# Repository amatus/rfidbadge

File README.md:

# RFID badge for DEF CON

## Controls

Press MENU to enter the menu system and to advance the selection.
Press SELECT to activate the selection.

Hold MENU to adjust the LCD contrast down (if the screen is all black).
Hold SELECT to adjust the LCD contrast up (if the screen is too light).

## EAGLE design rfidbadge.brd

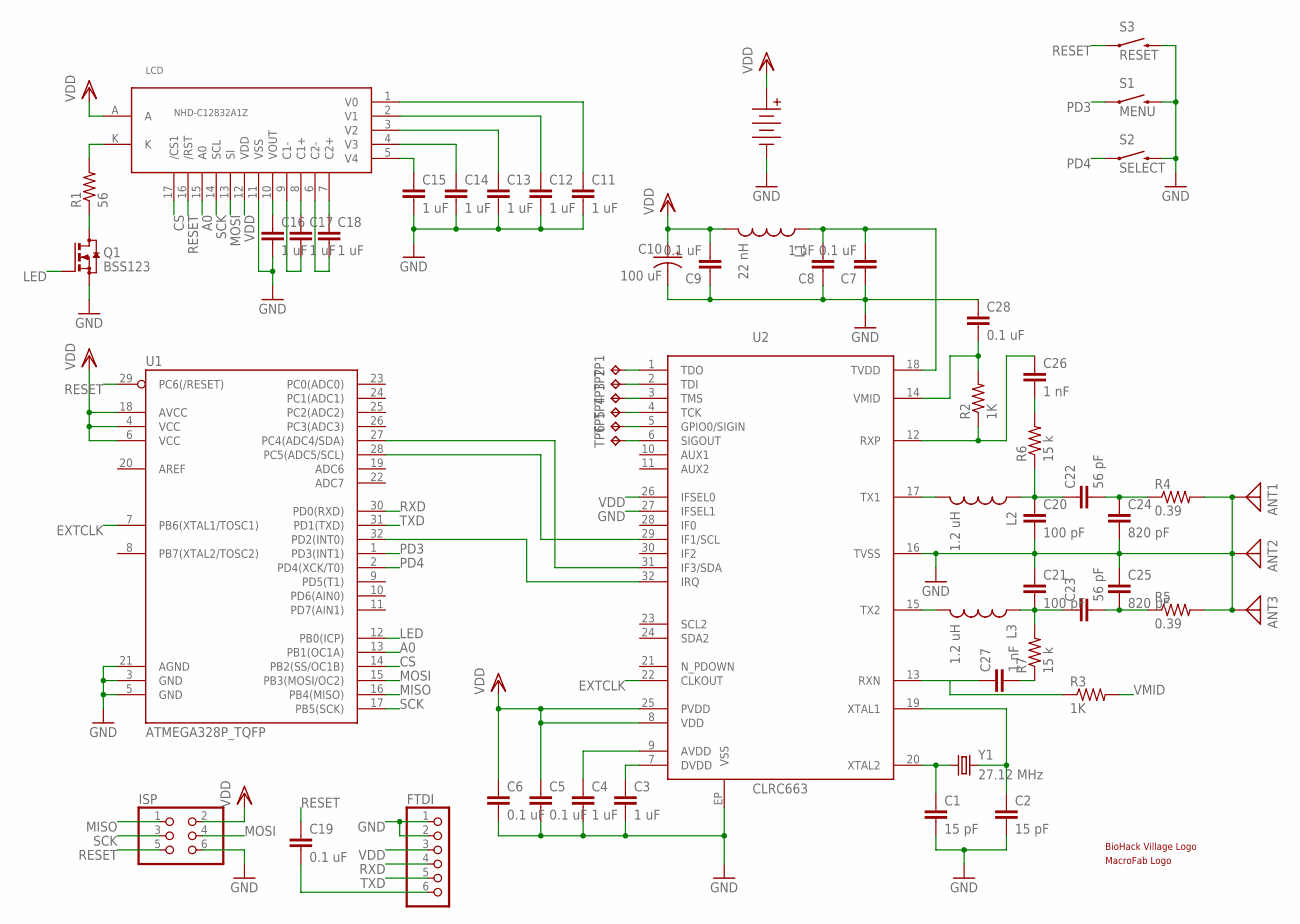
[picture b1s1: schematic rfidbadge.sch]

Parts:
ANT1, ANT2, ANT3: ANTENNA; PAD-01
BAT: AAA_X3
C1, C2: 15 pF; C0603K
C3, C4, C8, C11, C12, C13, C14, C15, C16, C17, C18: 1 uF; C0603K
C5, C6, C7, C9, C19, C28: 0.1 uF; C0603K
C10: 100 uF; EIA7343
C20, C21: 100 pF; C0603K
C22, C23: 56 pF; C0603K
C24, C25: 820 pF; C0603K
C26, C27: 1 nF; C0603K
FTDI: PINHD-1X6; 1X06
ISP: PINHD-2X3; 2X03
L1: 22 nH; 0603
L2, L3: 1.2 uH; 0603
LCD: NHD-C12832A1Z
Q1: BSS123; SOT23
R1: 56; R0603
R2, R3: 1K; R0603
R4, R5: 0.39; R0603
R6, R7: 15 k; R0603
S1: MENU; TACTILE_SWITCH_TALL
S2: SELECT; TACTILE_SWITCH_TALL
S3: RESET; TACTILE-SWITCH-1101NE
TP1, TP2, TP3, TP4, TP5, TP6: TPTP06R; TP06R
U1: ATMEGA328P_TQFP; TQFP32-08
U2: CLRC663; QFN32
U$1: BHVLOGO
U$2: MACROFABLOGO
Y1: 27.12 MHz; CRYSTAL-SMD-5X3

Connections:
A0: LCD.15 (A0), U1.13 (PB1(OC1A))
C1+: C17.1, LCD.8 (C1+)
C1-: C17.2, LCD.9 (C1-)
C2+: C18.1, LCD.7 (C2+)
C2-: C18.2, LCD.6 (C2-)
CS: LCD.17 (/CS1), U1.14 (PB2(SS/OC1B))
EXTCLK: U1.7 (PB6(XTAL1/TOSC1)), U2.22 (CLKOUT)
GND: ANT1.1, ANT2.1, ANT3.1, BAT.NEG, C1.2, C2.2, C3.2, C4.2, C5.2, C6.2, C7.1, C8.1, C9.1, C10.C (-), C11.2, C12.2, C13.2, C14.2, C15.2, C16.2, C20.2, C21.1, C24.2, C25.1, C28.1, FTDI.1, FTDI.2, ISP.6, LCD.11 (VSS), Q1.2 (S), R4.2, R5.2, S1.B2 (2), S2.B2 (2), S3.2, U1.3 (GND), U1.5 (GND), U1.21 (AGND), U2.16 (TVSS), U2.27 (IFSEL1), U2.EP (VSS)
K: LCD.K, R1.2
LED: Q1.1 (G), U1.12 (PB0(ICP))
MISO: ISP.1, U1.16 (PB4(MISO))
MOSI: ISP.4, LCD.13 (SI), U1.15 (PB3(MOSI/OC2))
unnamed: C20.1, C22.1, L2.1, R6.1
unnamed: C21.2, C23.1, L3.1, R7.2
unnamed: C22.2, C24.1, R4.1
unnamed: C23.2, C25.2, R5.1
unnamed: TP1.TP, U2.1 (TDO)
unnamed: TP2.TP, U2.2 (TDI)
unnamed: C26.2, R6.2
unnamed: C27.2, R7.1
unnamed: C27.1, R3.1, U2.13 (RXN)
unnamed: C4.1, U2.9 (AVDD)
unnamed: C3.1, U2.7 (DVDD)
unnamed: TP3.TP, U2.3 (TMS)
unnamed: TP4.TP, U2.4 (TCK)
unnamed: TP5.TP, U2.5 (GPIO0/SIGIN)
unnamed: TP6.TP, U2.6 (SIGOUT)
unnamed: Q1.3 (D), R1.1
unnamed: C19.2, FTDI.6
PD2: U1.32 (PD2(INT0)), U2.32 (IRQ)
PD3: S1.A2 (1), U1.1 (PD3(INT1))
PD4: S2.A2 (1), U1.2 (PD4(XCK/T0))
RESET: C19.1, ISP.5, LCD.16 (/RST), S3.1, U1.29 (PC6(/RESET))
RXD: FTDI.4, U1.30 (PD0(RXD))
RXP: C26.1, R2.1, U2.12 (RXP)
SCK: ISP.3, LCD.14 (SCL), U1.17 (PB5(SCK))
SCL: U1.28 (PC5(ADC5/SCL)), U2.29 (IF1/SCL)
SDA: U1.27 (PC4(ADC4/SDA)), U2.31 (IF3/SDA)
TVDD: C7.2, C8.2, L1.1, U2.18 (TVDD)
TX1: L2.2, U2.17 (TX1)
TX2: L3.2, U2.15 (TX2)
TXD: FTDI.5, U1.31 (PD1(TXD))
V0: C11.1, LCD.1 (V0)
V1: C12.1, LCD.2 (V1)
V2: C13.1, LCD.3 (V2)
V3: C14.1, LCD.4 (V3)
V4: C15.1, LCD.5 (V4)
VDD: BAT.POS, C5.1, C6.1, C9.2, C10.A (+), FTDI.3, ISP.2, L1.2, LCD.12 (VDD), LCD.A, U1.4 (VCC), U1.6 (VCC), U1.18 (AVCC), U2.8 (VDD), U2.25 (PVDD), U2.26 (IFSEL0)
VMID: C28.2, R2.2, R3.2, U2.14 (VMID)
VOUT: C16.1, LCD.10 (VOUT)
XTAL1: C2.1, U2.19 (XTAL1), Y1.3 (2)
XTAL2: C1.1, U2.20 (XTAL2), Y1.1

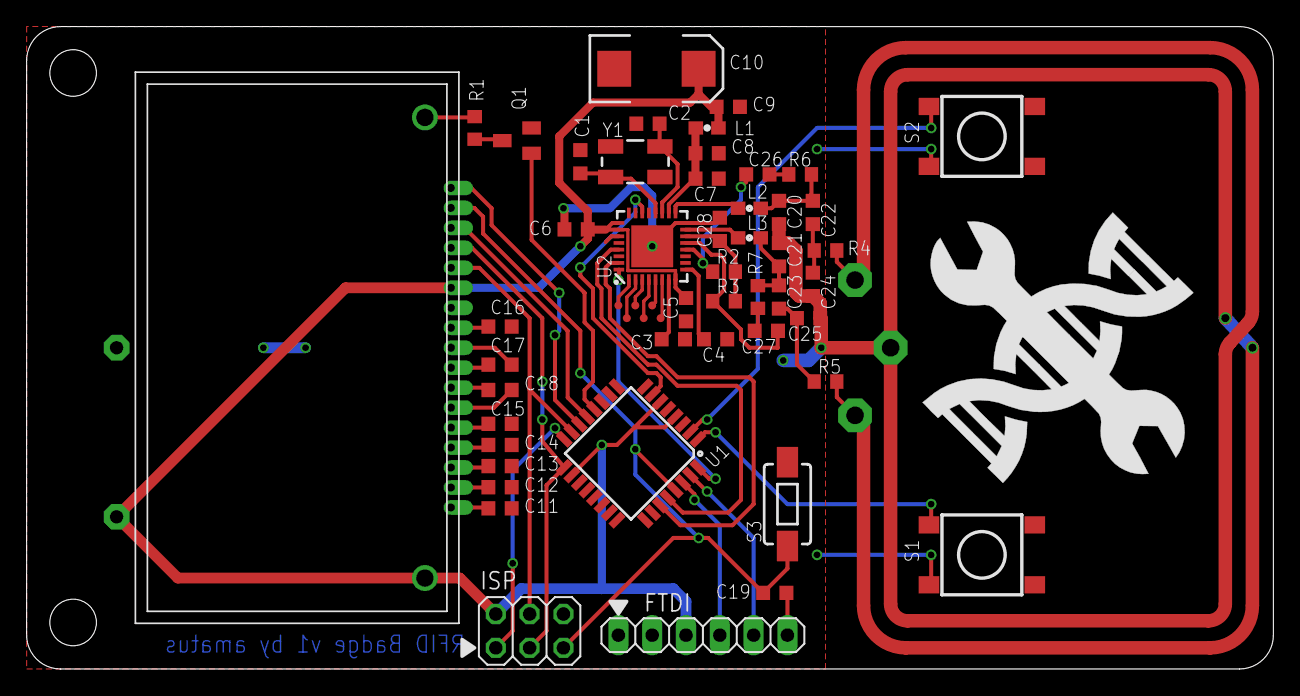
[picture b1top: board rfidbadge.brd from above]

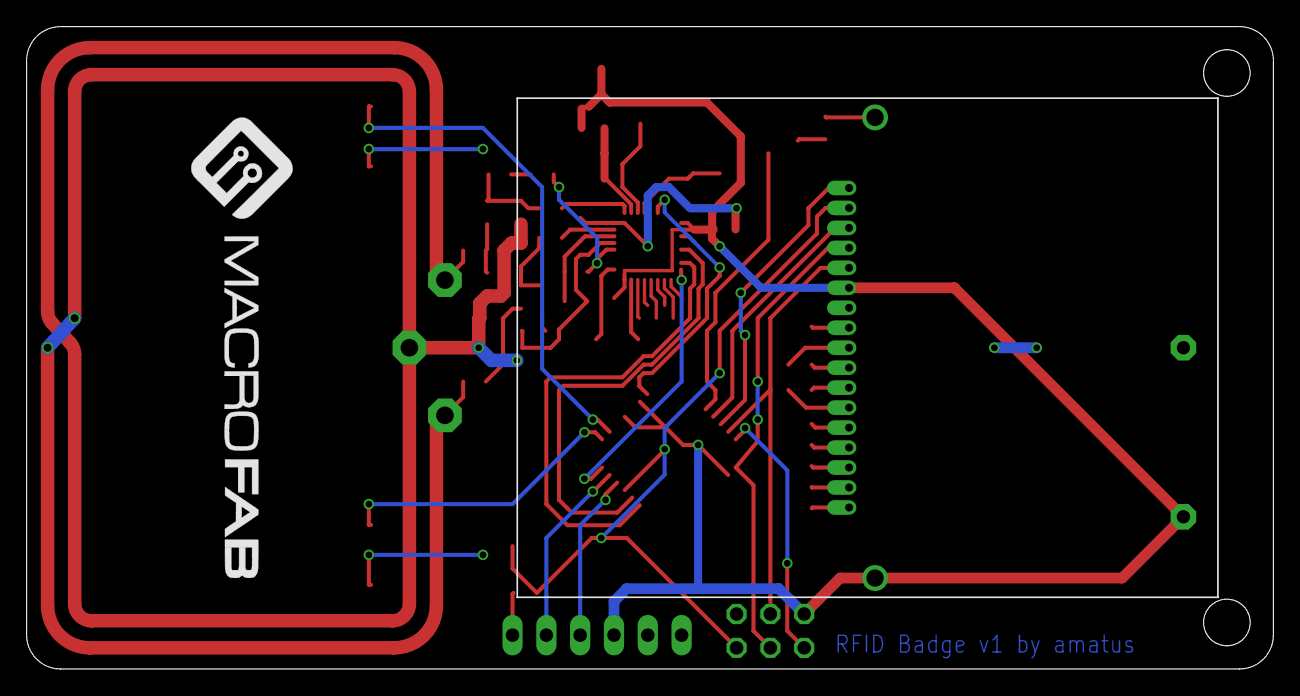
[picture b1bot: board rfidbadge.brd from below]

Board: 2 copper layers, 93.7 x 48.2 mm, 60 parts (2 on the bottom side), 52 nets.

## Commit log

2016-05-03 ATmega328 and CLRC663 parts and a blank schematic
2016-05-03 Wired up power and a crystal
2016-05-03 Added display and wired up I2C
2016-05-03 Add ISP and FTDI headers
2016-05-04 Add antenna circuit
2016-05-04 Add AAAx3 battery holder
2016-05-04 Interrupted in the middle of starting the board
2016-05-06 Lots of layout
2016-05-10 Add antenna trace and ground planes
2016-05-10 Finish routing
2016-05-11 Add switches, lanyard holes, rounded corners
2016-05-13 I like fat traces and I cannot lie
2016-05-14 Added some test pads
2016-05-15 Fix ground loops and islands
2016-05-18 Fix button grounds
2016-05-25 Some part values
2016-05-25 Values and part numbers complete
2016-05-26 Switch part number
2016-05-28 Fix orphaned ground plane
2016-06-03 Test Arduino sketch
2016-06-04 s/CLRC633/CLRC663/
2016-06-04 Send request type A and print results
2016-06-07 Add code to drive the display
2016-06-07 Adjust contrast for 4.5V
2016-06-07 Don't waste RAM.
2016-06-07 Fix start column
2016-06-07 We don't need pages 4-7 or a RMW cycle
2016-06-08 Connect IRQ line, move buttons
2016-06-08 Place part names
2016-06-08 Add reset switch
2016-06-10 Test buttons
2016-06-10 Make holes big enough for lobster claw
2016-06-11 Add Defcon 24 logo
2016-06-11 Fix artwork
2016-06-11 Add CAM job
2016-06-16 Read and dsiplay UID
2016-06-24 Replace DEF CON 24 logo with BioHack Village logo
2016-06-25 Indicate pin 1 on the headers
2016-06-27 Add MacroFab logo and cam job
2016-07-03 Increase diameter of BAT annulus for soldering
2016-07-03 Add sketch for programming the CLRC663 EEPROM
2016-07-14 Use EEPROM to store scan period
2016-07-16 Refactor interrupt code a bit
2016-07-17 Add a menu system
2016-07-17 User configurable scanning frequency
2016-07-23 Programmer sketch
2016-07-23 Document the bootstrap sketch
2016-07-23 Use arrow for menu selection
2016-07-26 Add contrast adjust
2016-07-26 Fix bool -> boolean
2016-07-26 Change types to match EEPROM.h

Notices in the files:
parts and their libraries:
SparkFun-DigitalIC: Licensing: Creative Commons ShareAlike 4.0 International - https://creativecommons.org/licenses/by-sa/4.0
